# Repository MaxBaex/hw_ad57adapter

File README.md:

# hw_ad57adapter
AD57 Vario Hardware adapter

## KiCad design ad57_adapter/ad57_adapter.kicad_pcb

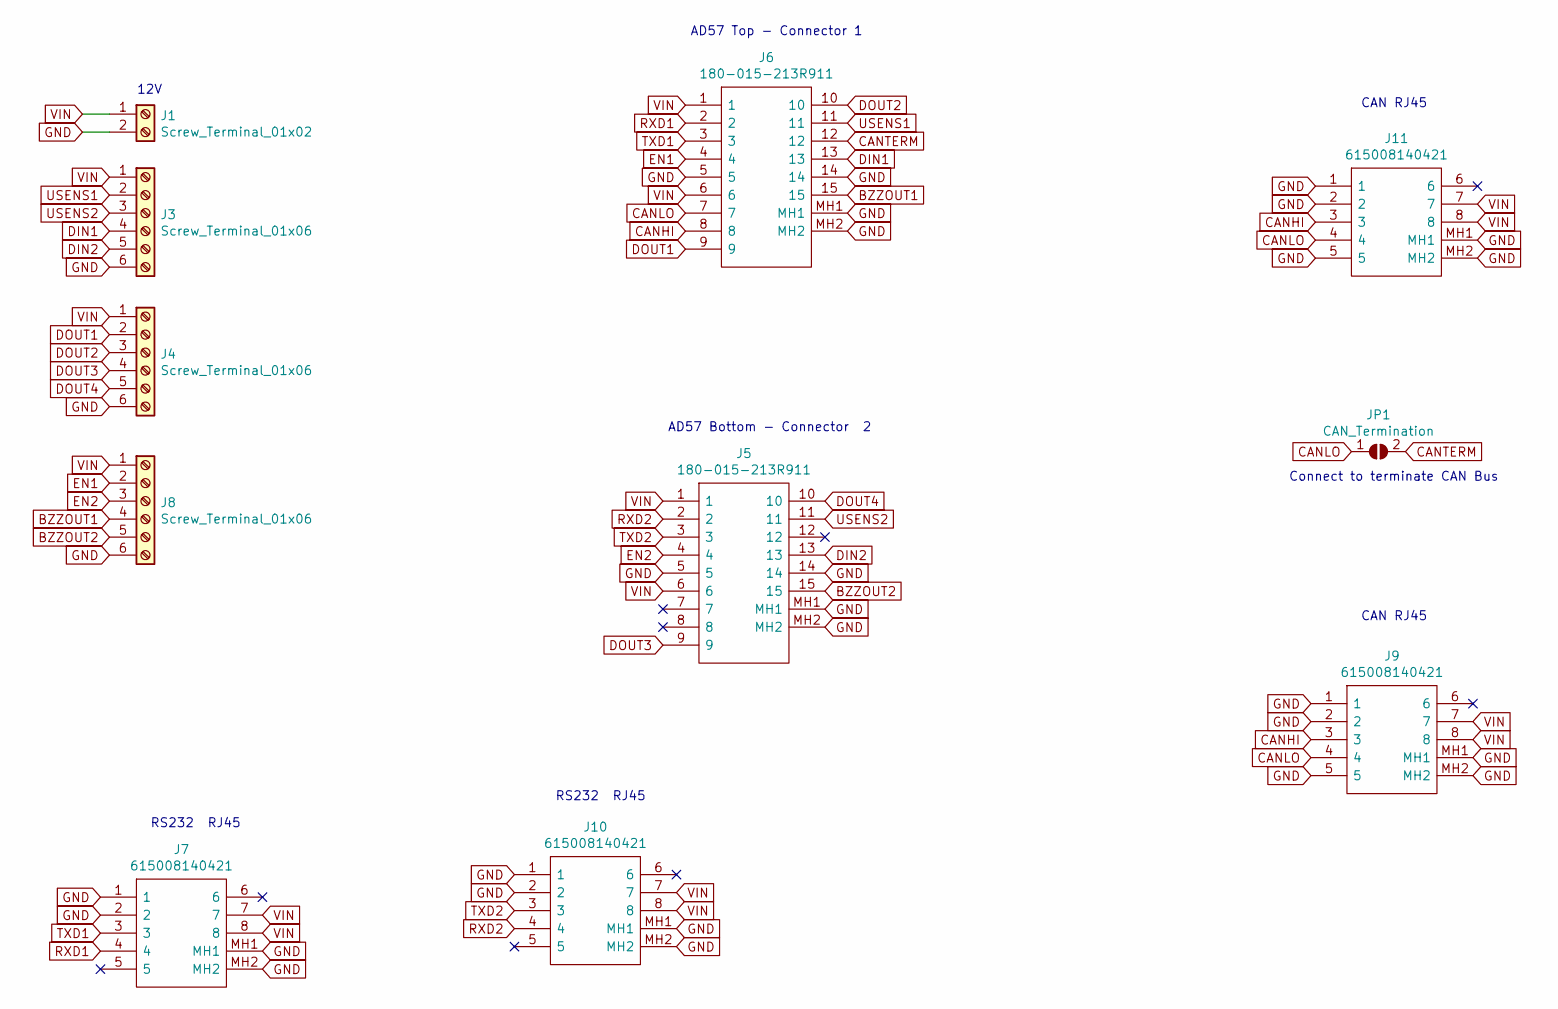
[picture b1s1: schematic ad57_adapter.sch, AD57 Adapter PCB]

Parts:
J1: Screw_Terminal_01x02; TerminalBlock_TE_282834-2_1x02_P2.54mm_Horizontal
J3, J4, J8: Screw_Terminal_01x06; TerminalBlock_TE_282834-6_1x06_P2.54mm_Horizontal
J5, J6: 180-015-213R911; 180015213R911; Mouser Part Number 636-180-015-213R911
J7, J9, J10, J11: 615008140421; Mouser Part Number 710-615008140421
JP1: CAN_Termination; SolderJumper-2_P1.3mm_Open_Pad1.0x1.5mm

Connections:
BZZOUT1: J6.15, J8.4
BZZOUT2: J5.15, J8.5
CANHI: J6.8, J9.3, J11.3
CANLO: J6.7, J9.4, J11.4, JP1.1 (A)
CANTERM: J6.12, JP1.2 (B)
DIN1: J3.4, J6.13
DIN2: J3.5, J5.13
DOUT1: J4.2, J6.9
DOUT2: J4.3, J6.10
DOUT3: J4.4, J5.9
DOUT4: J4.5, J5.10
EN1: J6.4, J8.2
EN2: J5.4, J8.3
GND: J1.2, J3.6, J4.6, J5.5, J5.14, J5.MH1, J5.MH2, J6.5, J6.14, J6.MH1, J6.MH2, J7.1, J7.2, J7.MH1, J7.MH2, J8.6, J9.1, J9.2, J9.5, J9.MH1, J9.MH2, J10.1, J10.2, J10.MH1, J10.MH2, J11.1, J11.2, J11.5, J11.MH1, J11.MH2
RXD1: J6.2, J7.4
RXD2: J5.2, J10.4
TXD1: J6.3, J7.3
TXD2: J5.3, J10.3
USENS1: J3.2, J6.11
USENS2: J3.3, J5.11
VIN: J1.1, J3.1, J4.1, J5.1, J5.6, J6.1, J6.6, J7.7, J7.8, J8.1, J9.7, J9.8, J10.7, J10.8, J11.7, J11.8

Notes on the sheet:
12V
AD57 Top - Connector 1
AD57 Bottom - Connector 2
RS232 RJ45
CAN RJ45
Connect to terminate CAN Bus

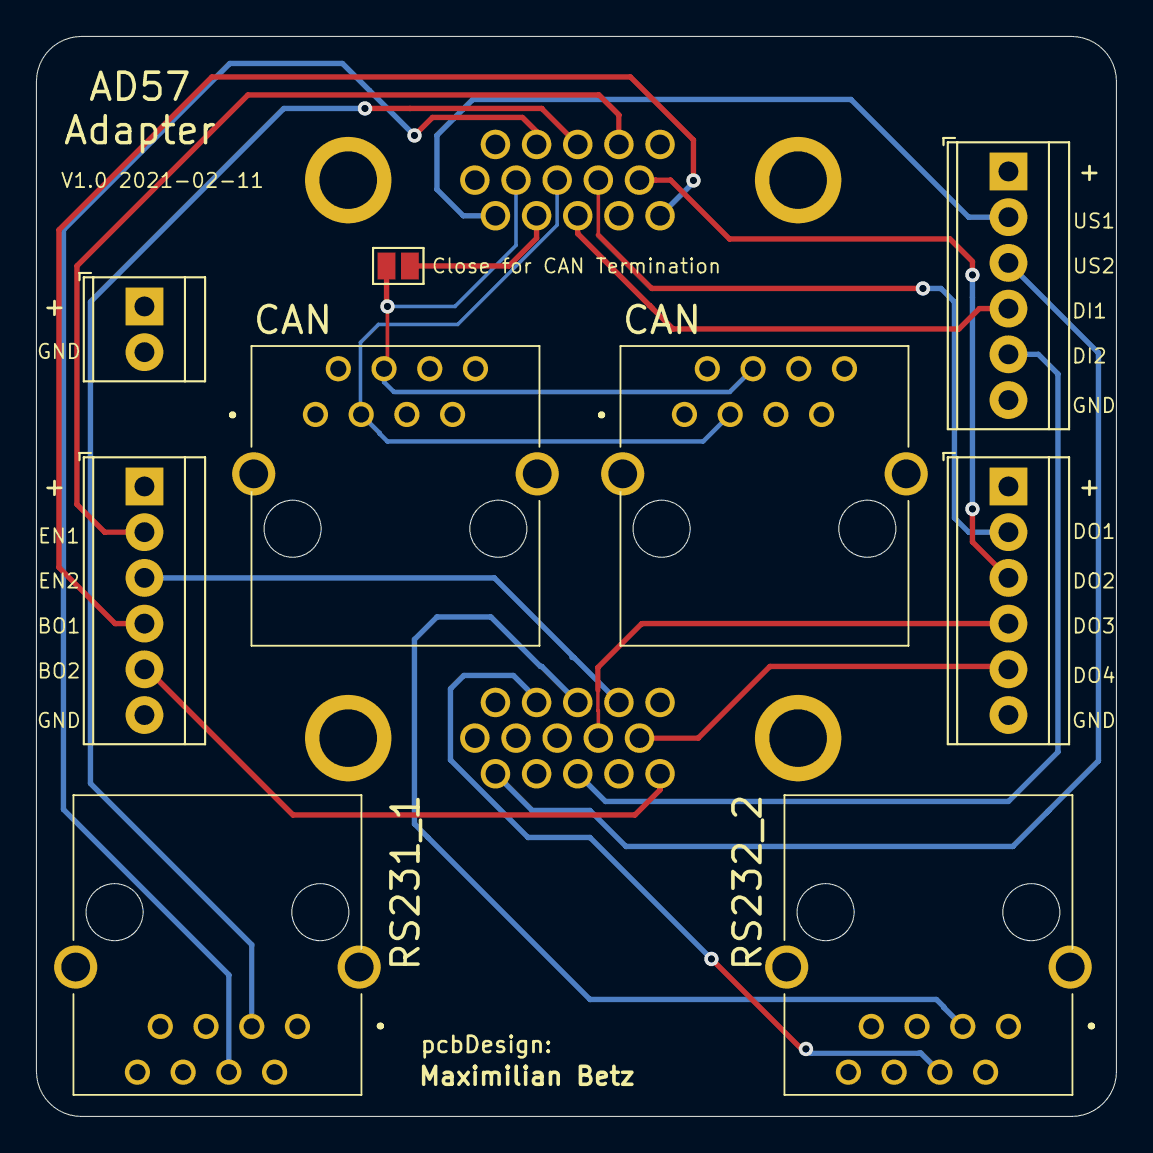
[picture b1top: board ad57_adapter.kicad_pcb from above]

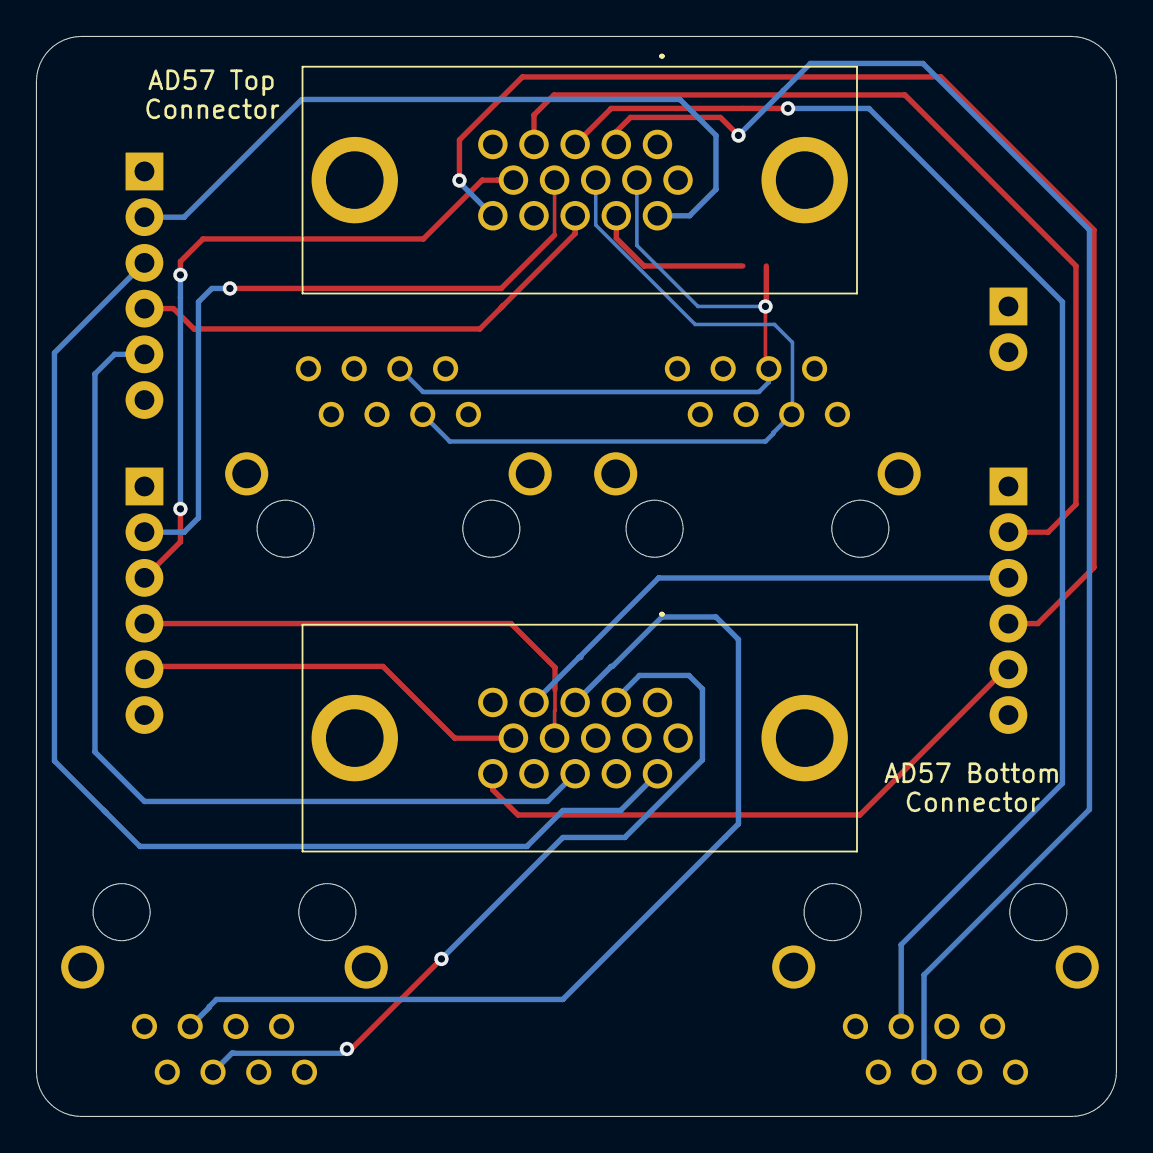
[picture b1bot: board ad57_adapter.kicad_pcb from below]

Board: 4 copper layers, 60.0 x 60.0 mm, 11 parts (2 on the bottom side), 21 nets.

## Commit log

2021-01-30 created project for adapter pcb.
2021-01-30 added a pdf schematic plot
2021-02-10 intial creation of pcb and updated schematic.
2021-02-10 connectors arranged. outline drawn
2021-02-10 finished routing.
2021-02-10 generated gerber. Schematic PDF export, 3D-View immages.
2021-02-12 this is the ordered version.
2021-03-01 Create README.md
    added a readme
2021-03-01 Update README.md
    readme
2021-03-09 added pcb picture
